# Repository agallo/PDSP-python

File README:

This script is designed to control a PDSP (or HDSP) type display using Python
when connected to a Raspberry Pi.

Things to do:
    * more flexible input via args (currently, using statically defined variable)
    * gracefully handle SIG-INT (ctrl-c) and clear display upon exit
    * for PBC - rearrange header pins to group unused pins so that a 1x6 header can be used
    
This code is based on Arduino code from http://www.nycresistor.com/2010/05/30/working-with-the-hdsp-2111/

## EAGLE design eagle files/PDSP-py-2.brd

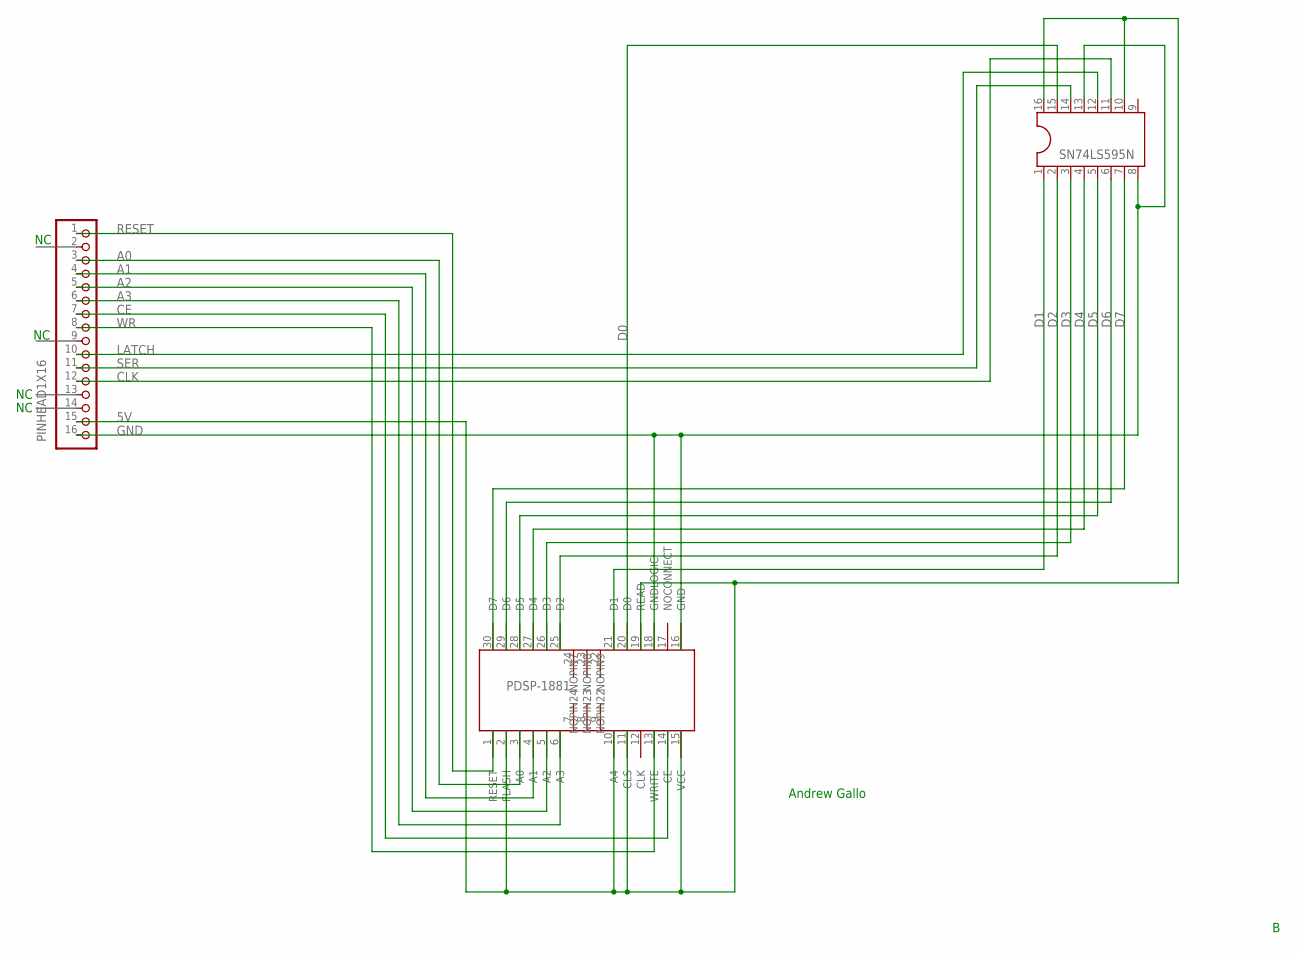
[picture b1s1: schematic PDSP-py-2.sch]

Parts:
PDSP-1881: AKG-PDSP-188-DEV; AKG-PDSP-188X-PAC
PINHEAD1X16: PINHD-1X16; 1X16
SN74LS595N: DIL16

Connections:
5V: PDSP-1881.2 (FLASH), PDSP-1881.10 (A4), PDSP-1881.11 (CLS), PDSP-1881.15 (VCC), PDSP-1881.19 (READ), PINHEAD1X16.15, SN74LS595N.10, SN74LS595N.16
A0: PDSP-1881.3 (A0), PINHEAD1X16.3
A1: PDSP-1881.4 (A1), PINHEAD1X16.4
A2: PDSP-1881.5 (A2), PINHEAD1X16.5
A3: PDSP-1881.6 (A3), PINHEAD1X16.6
CE: PDSP-1881.14 (CE), PINHEAD1X16.7
CLK: PINHEAD1X16.12, SN74LS595N.11
D0: PDSP-1881.20 (D0), SN74LS595N.15
D1: PDSP-1881.21 (D1), SN74LS595N.1
D2: PDSP-1881.25 (D2), SN74LS595N.2
D3: PDSP-1881.26 (D3), SN74LS595N.3
D4: PDSP-1881.27 (D4), SN74LS595N.4
D5: PDSP-1881.28 (D5), SN74LS595N.5
D6: PDSP-1881.29 (D6), SN74LS595N.6
D7: PDSP-1881.30 (D7), SN74LS595N.7
GND: PDSP-1881.16 (GND), PDSP-1881.18 (GNDLOGIC), PINHEAD1X16.16, SN74LS595N.8, SN74LS595N.13
LATCH: PINHEAD1X16.10, SN74LS595N.12
RESET: PDSP-1881.1 (RESET), PINHEAD1X16.1
SER: PINHEAD1X16.11, SN74LS595N.14
WR: PDSP-1881.13 (WRITE), PINHEAD1X16.8

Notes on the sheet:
Andrew Gallo

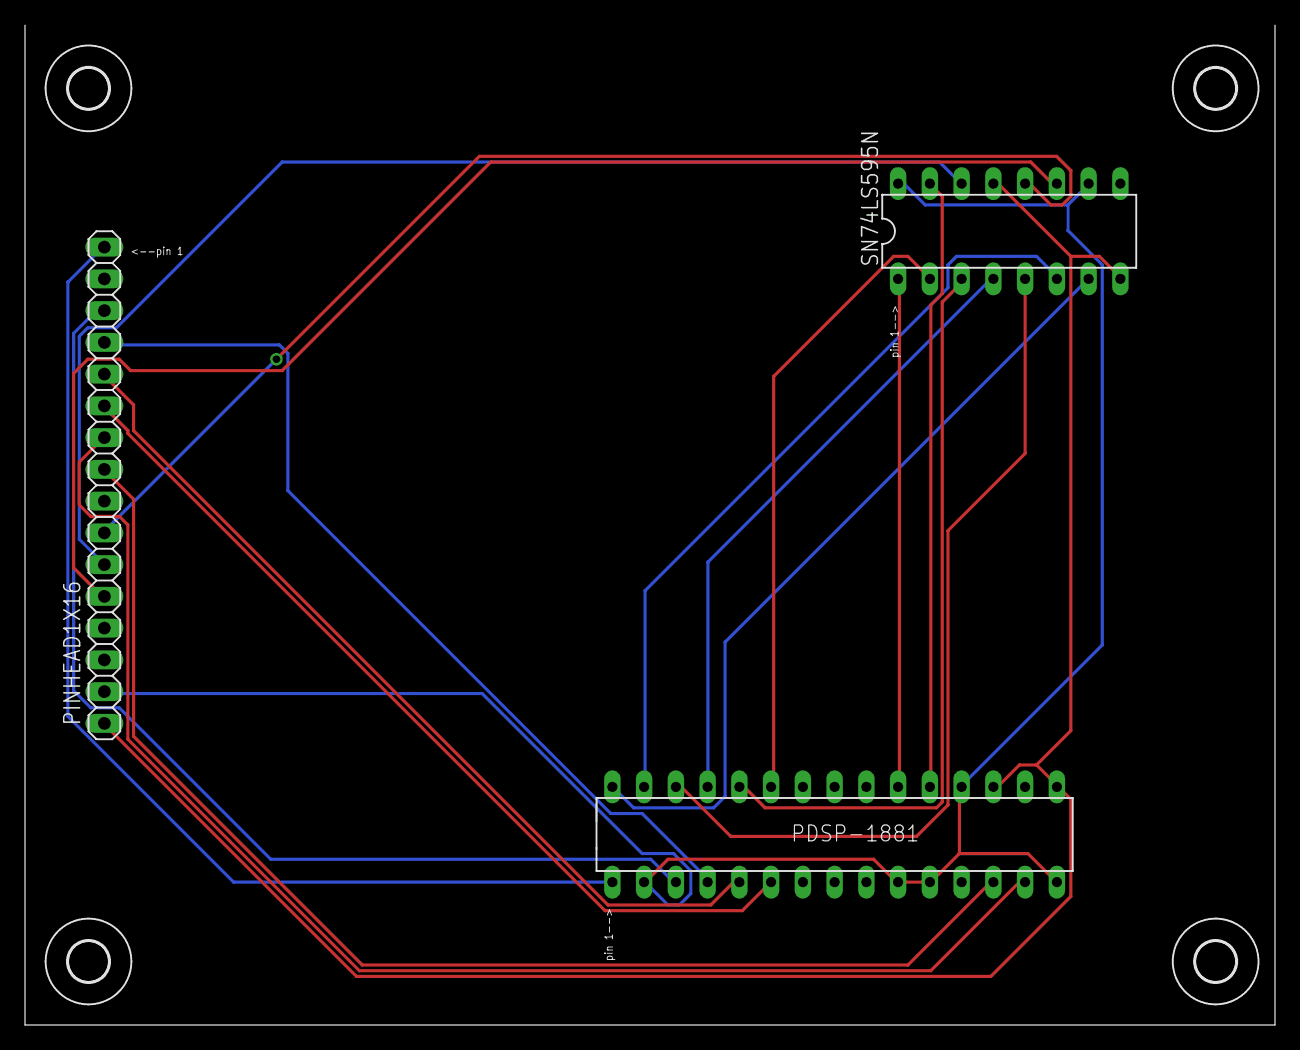
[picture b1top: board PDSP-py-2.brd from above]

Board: 2 copper layers, 100.0 x 80.0 mm, 7 parts (0 on the bottom side), 20 nets.

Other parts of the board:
U$1, U$2, U$3, U$4: 3,2

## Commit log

2015-02-23 PDSPinPy try 3
2015-02-23 adding readme
2015-02-23 removing unused import
2015-03-01 initial upgrade to use GPIO
2015-03-01 pin documentation and pinMode setup
2015-03-02 added reset display function
2015-03-02 code cleanup
2015-03-03 adding wiringpi2 code
2015-05-27 adding address binary AND logic
2015-05-27 correcting address ping code in writedisplay
2015-06-07 adding ord() to wiringpi.shiftOut() (line 112) because this seems to what an int, not a char
2015-06-08 changing setup pins from numbers to variables (and removing a duplicate pinMode statement)
2015-06-08 changing clock pin and correcting Shift Register type
2015-06-10 changing CLK pin to 18
2015-06-10 adjusting sleep timers
2015-06-10 Update PDSPinPy-3.py
    minor formatting edits
2015-06-10 Update PDSPinPy-3.py
    deleting TODO for wiringpi;
    adding TODO for SIG-INT handling
2015-06-14 adding header pin details in the comments
2015-07-02 documentation and comments updated
2015-07-02 adding eagle files
